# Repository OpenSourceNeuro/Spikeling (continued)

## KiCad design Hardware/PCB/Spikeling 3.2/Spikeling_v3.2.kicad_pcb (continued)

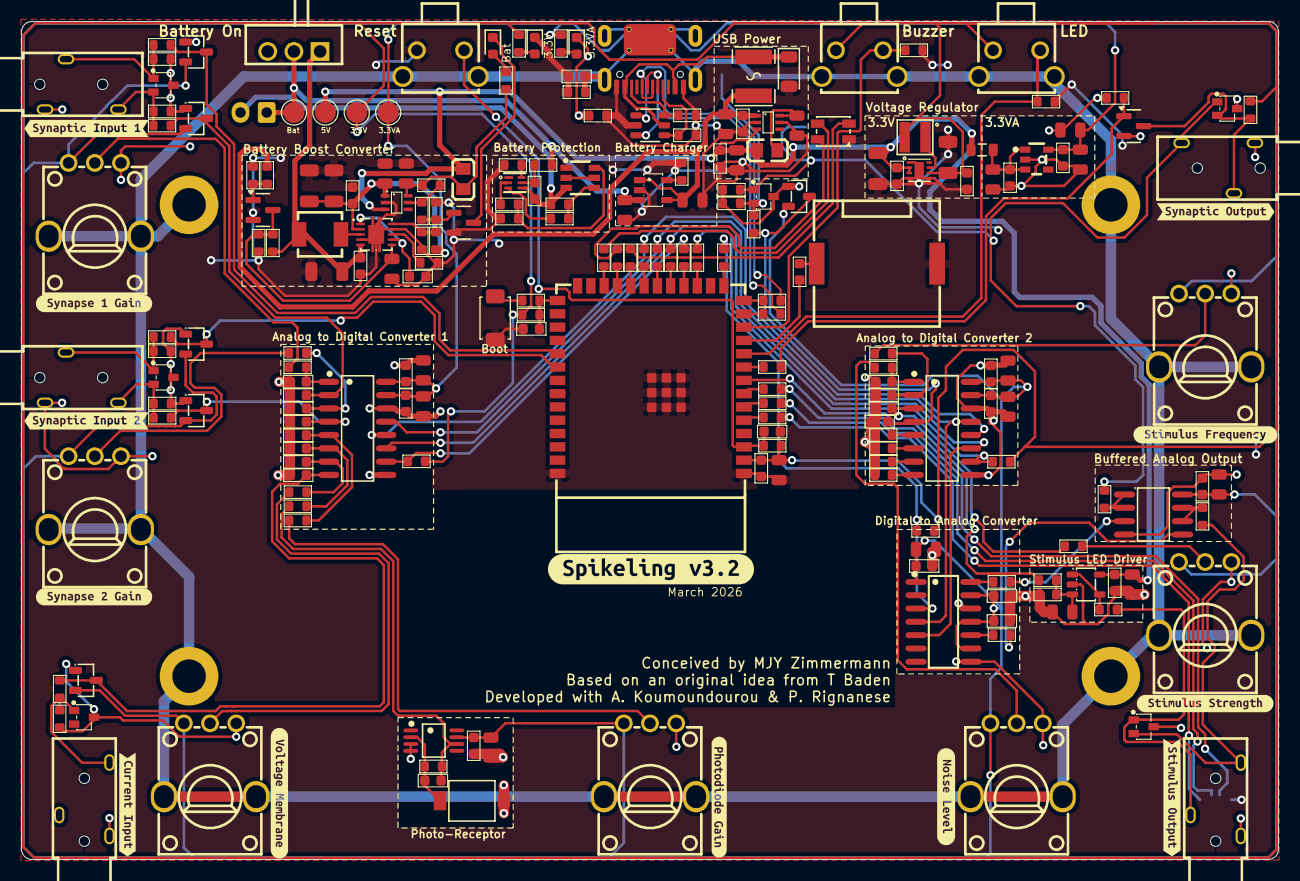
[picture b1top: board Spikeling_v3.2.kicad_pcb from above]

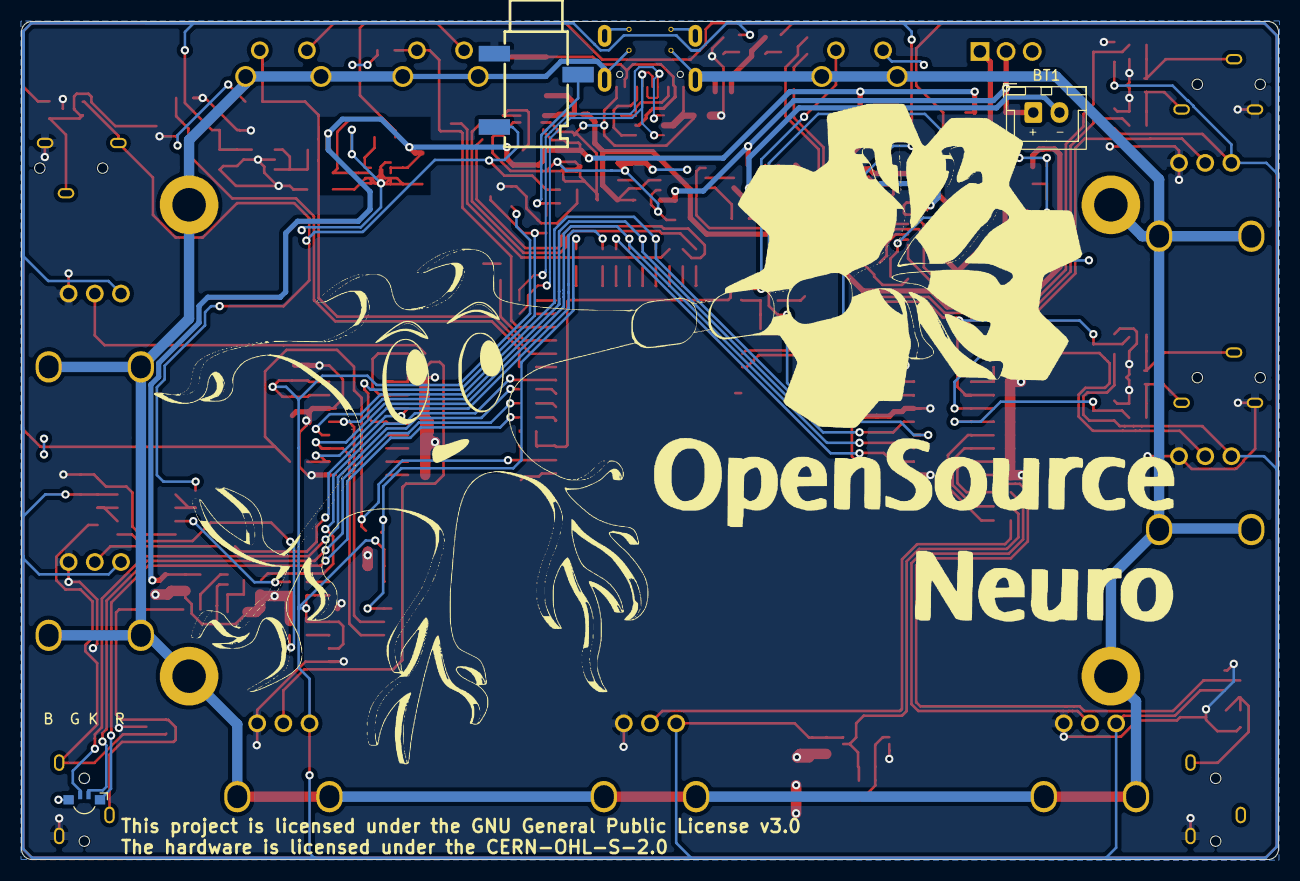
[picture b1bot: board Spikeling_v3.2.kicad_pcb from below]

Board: 2 copper layers, 120.0 x 80.0 mm, 232 parts (3 on the bottom side), 121 nets.

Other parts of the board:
kibuzzard-699ADA5F: G***; kibuzzard-699ADA5F
kibuzzard-699ADA80: G***; kibuzzard-699ADA80
kibuzzard-699ADAA1: G***; kibuzzard-699ADAA1
kibuzzard-699ADACE: G***; kibuzzard-699ADACE
kibuzzard-699ADAEF: G***; kibuzzard-699ADAEF
kibuzzard-699ADB2E: G***; kibuzzard-699ADB2E
kibuzzard-699ADB4A: G***; kibuzzard-699ADB4A
kibuzzard-699ADBA0: G***; kibuzzard-699ADBA0
kibuzzard-699ADBCD: G***; kibuzzard-699ADBCD
kibuzzard-699ADBE4: G***; kibuzzard-699ADBE4
kibuzzard-699ADC07: G***; kibuzzard-699ADC07
kibuzzard-699ADC8D: G***; kibuzzard-699ADC8D
kibuzzard-699AE09E: G***; kibuzzard-699AE09E

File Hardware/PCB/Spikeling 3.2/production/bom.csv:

Designator,Footprint,Quantity,Value,LCSC Part #
B1,BUZ-TH_L12.0-W12.0,1,4kHz,C7421651
BT1,JST_XH_B2B-XH-A_1x02_P2.50mm_Vertical,1,Battery_Cell,C265283
"C1, C55",C_0603,2,1nF,C100040
"C10, C12, C13, C18, C21, C23, C27, C28, C3, C30, C32, C33, C35, C37, C39, C42, C44, C45, C47, C49, C51, C53, C56, C57, C58, C6, C60, C62, C64, C8",C_0603,30,100nF,C1591
"C11, C14, C2, C24, C25, C26, C36, C4, C40, C61",C_0805,10,1uF,C28323
"C15, C16, C17, C29, C31, C34, C38, C5, C52, C59",C_0805,10,4.7uF,C694229
"C19, C20, C9",C_1206,3,22uF,C12891
"C22, C7",C_1206,2,10uF,C2171160
C41,C_0805,1,10uF,C2932476
C43,C_0603,1,4.7nF,C53987
"C46, C48, C50, C63",C_0603,4,10nF,C100042
C54,C_0603,1,10pF,C91367
D1,D_SOD-123FL,1,SMF6.0A,C178260
"D10, D12, D19, D6, D7, D9",SOT-23-3_L2.9-W1.3-P1.90-LS2.4-BR,6,BAT54S,C916425
"D11, D14, D17, D18, D5, D8",SC-70-3_L2.0-W1.3-P0.65-LS2.1-BL,6,TPD2E2U06DCKR,C1855726
D13,SENSOR-TH_BPW34S-Z,1,BPW34S-Z,C67891
D15,LED_Kingbright_APFA3010_3x1.5mm_Horizontal,1,LED_BGKR,
D16,LED-SMD_4P-L3.2-W2.8-BL,1,MHPC3528CRGBCT,C2962096
"D2, D3",D_0603,2,Red,C2286
D4,D_0603,1,Yellow,C89811
J1,TYPE-C-SMD_HX-TYPE-C-16PIN,1,"Connector, USB-TYPE-C-16P",C2927039
J2,AUDIO-SMD_HX-PJ-320A-3P-DIP,1,Synapse1 In,C19189087
J3,AUDIO-SMD_HX-PJ-320A-3P-DIP,1,Synapse2 In,C19189087
J4,AUDIO-SMD_HX-PJ-320A-3P-DIP,1,Input Current,C19189087
J5,AUDIO-SMD_HX-PJ-320A-3P-DIP,1,Stimulus Out,C19189087
J6,AUDIO-SMD_HX-PJ-320A-3P-DIP,1,Synapse Out,C19189087
J7,AUDIO-SMD_PJ-320B,1,Oscilloscope Output,C18594
"L1, L5",L0805,2,BLM21PG221SN1D,C85840
L2,IND-SMD_L3.0-W3.0_XFL3012,1,2.2uH,C3911432
L3,L_0805,1,MPZ2012S601,C21519
L4,IND-SMD_L4.4-W4.0_PHC0420,1,2.2uH,C5349665
Q1,SOT-23-6_L2.9-W1.6-P0.95-LS2.8-BR,1,FS8205A,C908265
"Q2, Q3, Q4",Q_SOT-23,3,2N7002,C8545
"R1, R16, R18, R24, R61",R_0603,5,1MΩ,C105578
"R10, R8",R_0603,2,5.1MΩ,C227984
"R11, R23, R26, R27, R45, R69, R70, R71, R72, R73, R74, R9",R_0603,12,100Ω,C115420
R12,R_0603,1,2.2kΩ,C4190
R13,R_0603,1,330Ω,C23138
R14,R_0603,1,910kΩ,C2907075
"R15, R17, R19, R20, R21, R31, R32, R33, R34, R48, R49, R53, R54, R59, R67, R77, R80, R81",R_0603,18,100kΩ,C14675
"R2, R22, R3, R4, R5",R_0603,5,5.1kΩ,C23186
"R25, R30, R35, R44, R46, R66, R75, R78, R79",R_0603,9,10kΩ,C2906982
"R28, R29",R_0603,2,220Ω,C22962
"R36, R37",R_0603,2,22Ω,C23345
"R38, R39, R40, R41, R42, R43",R_0603,6,47Ω,C23182
"R47, R50, R51, R52, R55, R56, R57, R58, R60, R62, R63, R64, R65, R76, R82",R_0603,15,1kΩ,C2907002
R6,R_0603,1,0Ω,C21189
R68,R_0603,1,150Ω,C22808
R7,R_0603,1,4.7kΩ,C23162
SW1,SW-TH_K3-1260D-L1,1,K3-1260D-L1,C92657
SW2,SW_TS-1088-AR02016,1,"Tactile Button, 160gf",C720477
"SW3, SW4, SW5",KEY-TH_4P-L7.5-W6.8-P4.50-LS7.2,3,SKHHLVA010, C2845277
"TP1, TP2, TP3, TP4",TestPoint_Pad_D2.0mm,4,TestPoint,
TV1,SOT-23-6_L2.9-W1.6-P0.95-LS2.8-BR,1,SRV05-4-P-T7,C85364
U1,F1812,1,MF-MSMF050-2,C17313
"U10, U11",SOIC-16_L9.9-W3.9-P1.27-LS6.0-BL,2,MCP3208T-CI/SL,C626764
U12,WIFIM-SMD_ESP32-S3-WROOM-1-N8,1,ESP32-S3-WROOM-1-N4,C2913197
U13,VSSOP-8_L3.0-W3.0-P0.65-LS4.9-BL,1,OPA380AIDGKR,C2057355
U14,SOT-23-5_L3.0-W1.7-P0.95-LS2.8-BR,1,TLV9001IDBVR,C398363
U15,SOIC-8_L4.9-W3.9-P1.27-LS6.0-BL,1,MCP6002T-I/SN,C7377
"U2, U8",SC-70-6_L2.0-W1.3-P0.65-LS2.1-BL,2,LM66100DCKR,C2869734
U3,WSON-8_L2.0-W2.0-P0.50-TL-EP,1,TPS62162DSGR,C40256
U4,SOT-23-5_L2.9-W1.6-P0.95-LS2.8-BR,1,TPS7A2033PDBVR,C2862740
U5,SOT-23-5_L3.0-W1.7-P0.95-LS2.8-BR,1,MCP73812T-420I/OT,C144308
U6,WSON-6_L1.5-W1.5-P0.50-TL,1,BQ29700DSER,C183096
U7,VSON-10_L3.0-W3.0-P0.50-TL-EP_TPS62410DRCR,1,TPS61200DRCR,C140320
U9,SOIC-14_L8.7-W3.9-P1.27-LS6.0-BL,1,MCP4922-E/SL,C39851
"VR1, VR2, VR3, VR4, VR6, VR7",RES-TH_RK09D1130C2P,6,10kΩ,C470316
VR5,RES-TH_RK09D1130C2P,1,10kΩ,C361173

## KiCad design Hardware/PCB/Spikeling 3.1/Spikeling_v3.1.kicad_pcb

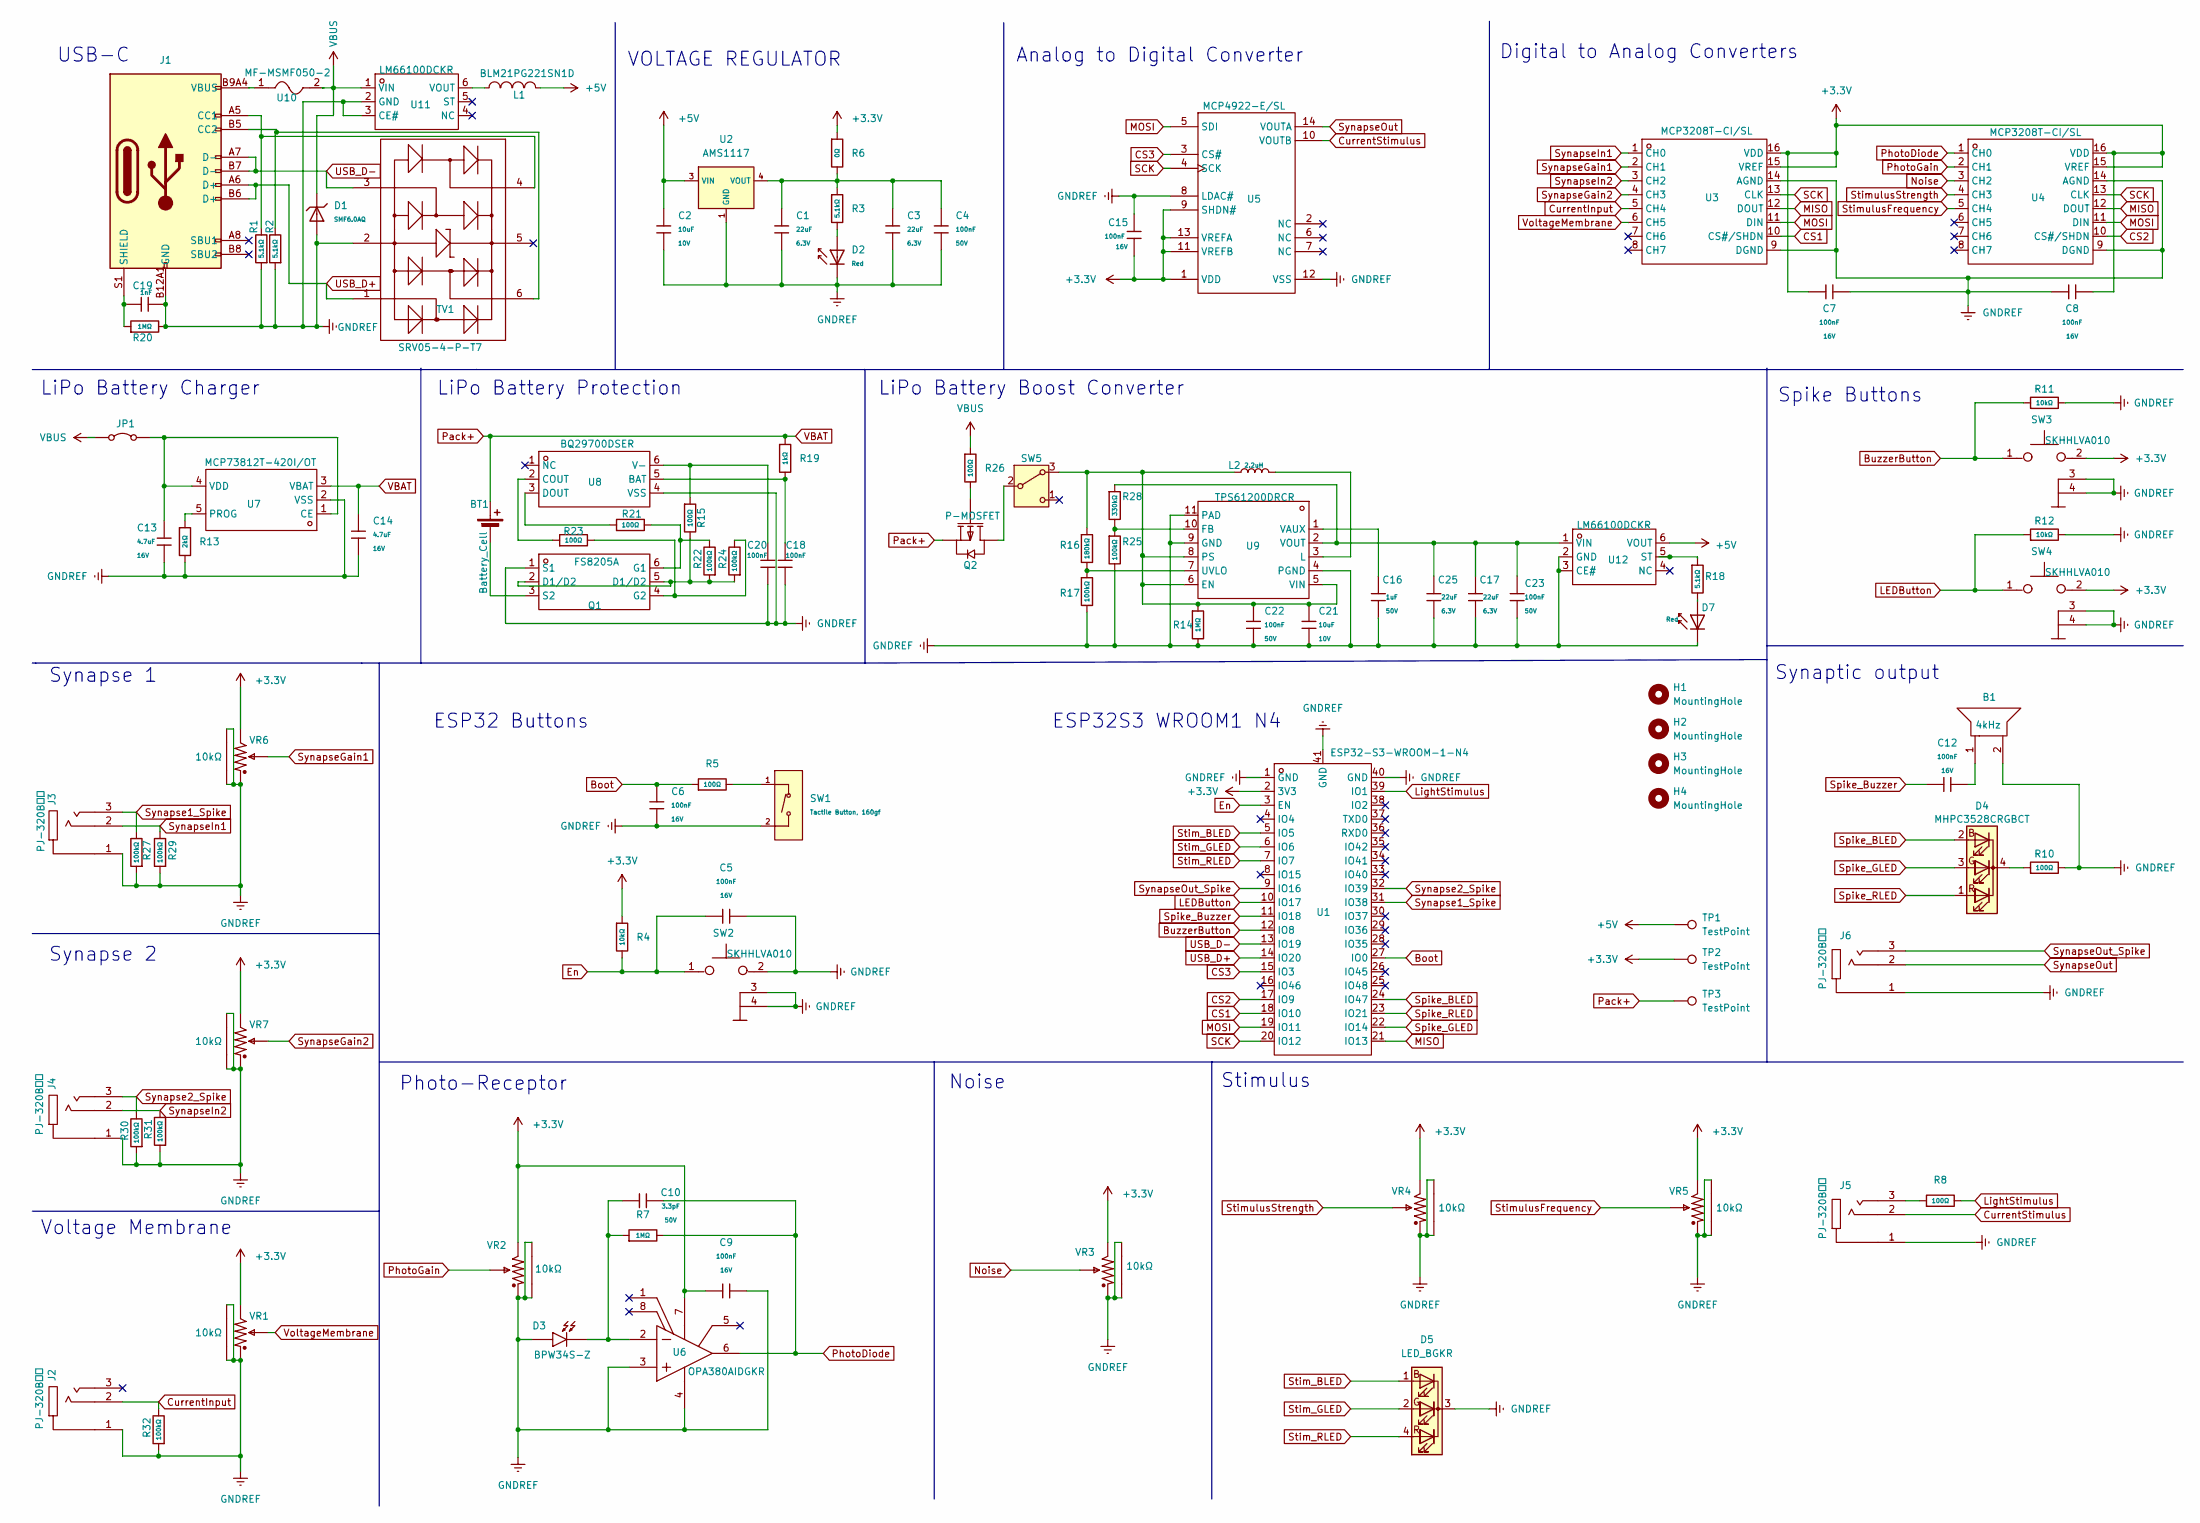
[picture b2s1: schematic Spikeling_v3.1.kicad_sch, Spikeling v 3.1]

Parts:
B1: 4kHz; BUZ-TH_L12.0-W12.0; LCSC Part # C7421651
BT1: Battery_Cell; JST_XH_B2B-XH-A_1x02_P2.50mm_Vertical; LCSC Part # C265283
C1, C3, C17, C25: 22uF; C_0603; Voltage Rated 6.3V; Tolerance ±20%; Part CL10A226MQ8NRNC; LCSC C59461
C2, C21: 10uF; C_0603; Voltage Rated 10V; Tolerance ±10%; Part CL10A106KP8NNNC; LCSC C19702
C4, C18, C20, C22, C23: 100nF; C_0603; Voltage Rated 50V; Tolerance ±10%; Part CC0603KRX7R9BB104; LCSC C14663
C5, C6, C7, C8, C9, C12, C15: 100nF; C_0402; Voltage Rated 16V; Tolerance ±10%; Part CL05B104KO5NNNC; LCSC C1525
C10: 3.3pF; C_0402; Voltage Rated 50V; Part 0402CG3R3C500NT; LCSC C1565
C13, C14: 4.7uF; C_0603; Voltage Rated 16V; Tolerance ±10%; Part CL10A475KO8NNNC; LCSC C19666
C16: 1uF; C_0603; Voltage Rated 50V; Tolerance ±10%; Part CL10A105KB8NNNC; LCSC C15849
C19: 1nF; C_0603; Voltage Rated 50V; Tolerance ±10%; Part CL10B102KB8NNNC; LCSC C1588
D1: SMF6.0AQ; D_SOD-123FL; Part SMF6.0AQ; LCSC Part # C20605188
D2, D7: Red; D_0603; Part KT-0603R; LCSC Part # C2286
D3: BPW34S-Z; SENSOR-TH_BPW34S-Z; MANUFACTURER PART BPW34S-Z; LCSC PART NAME 920nm 频谱范围420nm~1120nm 反向电压32V
D4: MHPC3528CRGBCT; LED-SMD_4P-L3.2-W2.8-BL; LCSC PART NAME RGB三色 正贴
D5: LED_BGKR; LED_D5.0mm-4_RGB_Wide_Pins
H1, H2, H3, H4: MountingHole; MountingHole_3mm
J1: Connector, USB-TYPE-C-16P; TYPE-C-SMD_HX-TYPE-C-16PIN; LCSC Part # C2927039
J2, J3, J4, J5, J6: PJ-320B贴片; AUDIO-SMD_PJ-320B; CURRENT RATING (MAX) 200mA; VOLTAGE RATING (MAX) 30V; MANUFACTURER PART PJ-320B贴片; LCSC PART NAME 3.5mm耳机座
JP1: Jumper; SolderJumper-2_P1.3mm_Open_Pad1.0x1.5mm
L1: BLM21PG221SN1D; L0805; TOLERANCE ±25%; CURRENT RATING 2A; MANUFACTURER PART BLM21PG221SN1D; LCSC PART NAME 单路 0805磁珠 阻抗220Ω@100MHz
L2: 2.2uH; L_0805; Tolerance ±10%; Part CMI201209U2R2KT; LCSC C1043
Q1: FS8205A; SOT-23-6_L2.9-W1.6-P0.95-LS2.8-BR; MANUFACTURER PART FS8205A; LCSC PART NAME 2个N沟道 耐压:20V 电流:6A
Q2: P-MOSFET; SOT-23-3_L2.9-W1.3-P1.90-LS2.4-BR; MANUFACTURER PART SI2309CDS-T1-GE3; LCSC PART NAME 1个P沟道 耐压:60V 电流:1.6A
R1, R2, R3, R18: 5.1kΩ; R_0603; Overload Voltage (Max) 75V; Tolerance ±1%; Part 0603WAF5101T5E; LCSC C23186
R4, R11, R12: 10kΩ; R_0603; Overload Voltage (Max) 75V; Tolerance ±1%; Part 0603WAF1002T5E; LCSC C25804
R5, R8, R10, R15, R21, R23, R26: 100Ω; R_0603; Overload Voltage (Max) 75V; Tolerance ±1%; Part 0603WAF1000T5E; LCSC C22775
R6: 0Ω; R_0603; Overload Voltage (Max) 75V; Tolerance ±1%; Part 0603WAF0000T5E; LCSC C21189
R7, R14, R20: 1MΩ; R_0603; Overload Voltage (Max) 75V; Tolerance ±1%; Part 0603WAF1004T5E; LCSC C22935
R13: 2kΩ; R_0603; Overload Voltage (Max) 75V; Tolerance ±1%; Part 0603WAF2001T5E; LCSC C22975
R16: 180kΩ; R_0603; Overload Voltage (Max) 75V; Tolerance ±1%; Part 0603WAF1803T5E; LCSC C22827
R17, R22, R24, R25, R27, R29, R30, R31, R32: 100kΩ; R_0603; Overload Voltage (Max) 75V; Tolerance ±1%; Part 0603WAF1003T5E; LCSC C25803
R19: 1kΩ; R_0603; Overload Voltage (Max) 75V; Tolerance ±1%; Part 0603WAF1001T5E; LCSC C21190
R28: 330kΩ; R_0603; Overload Voltage (Max) 75V; Tolerance ±1%; Part 0603WAF3303T5E; LCSC C23137
SW1: Tactile Button, 160gf; SW_TS-1088-AR02016; Voltage Rating (Dc) 12V; Part TS-1088-AR02016; LCSC Part # C720477
SW2, SW3, SW4: SKHHLVA010; KEY-TH_4P-L7.5-W6.8-P4.50-LS7.2; VOLTAGE RATING (DC) 12V; MANUFACTURER PART SKHHLVA010; LCSC PART NAME 6*6*5.85mm 卧插 轻触开关
SW5: SW_Nidec_CAS-120A1; SW-TH_MMP122-R; LCSC Part # C92657
TP1, TP2, TP3: TestPoint; TestPoint_Pad_D2.0mm
TV1: SRV05-4-P-T7; SOT-23-6_L2.9-W1.6-P0.95-LS2.8-BR; CLAMPING VOLTAGE 12V; VOLTAGE - BREAKDOWN 6V; MANUFACTURER PART SRV05-4-P-T7; LCSC Part ESD 5V截止 峰值浪涌电流：1A@8/20us
U1: ESP32-S3-WROOM-1-N4; WIFIM-SMD_ESP32-S3-WROOM-1-N8; MANUFACTURER PART ESP32-S3-WROOM-1-N4; LCSC PART NAME 通用型Wi-Fi+低功耗蓝牙MCU模组
U2: AMS1117; SOT-223-3_L6.5-W3.4-P2.30-LS7.0-BR; Output Voltage 3.3V; Dropout Voltage 1.3V@(800mA); Part AMS1117-3.3; LCSC Part # C6186
U3, U4: MCP3208T-CI/SL; SOIC-16_L9.9-W3.9-P1.27-LS6.0-BL; VOLTAGE - SUPPLY 2.7V~5.5V; MANUFACTURER PART MCP3208T-CI/SL; LCSC PART NAME MCP3208T-CI/SL
U5: MCP4922-E/SL; SOIC-14_L8.7-W3.9-P1.27-LS6.0-BL; VOLTAGE - SUPPLY 2.7V~5.5V; VOLTAGE REFERENCE External; MANUFACTURER PART MCP4922-E/SL; LCSC PART NAME MCP4922-E/SL
U6: OPA380AIDGKR; VSSOP-8_L3.0-W3.0-P0.65-LS4.9-BL; MANUFACTURER PART OPA380AIDGKR; LCSC PART NAME OPA380AIDGKR
U7: MCP73812T-420I/OT; SOT-23-5_L3.0-W1.7-P0.95-LS2.8-BR; VOLTAGE - SUPPLY 3.75V~6V; MANUFACTURER PART MCP73812T-420I/OT; LCSC PART NAME 单节锂离子/聚合物电池充电管理控制器
U8: BQ29700DSER; WSON-6_L1.5-W1.5-P0.50-TL; VOLTAGE - SUPPLY -300mV~8V; MANUFACTURER PART BQ29700DSER; LCSC PART NAME BQ29700DSER
U9: TPS61200DRCR; VSON-10_L3.0-W3.0-P0.50-TL-EP_TPS62410DRCR; VOLTAGE - SUPPLY 300mV~5.5V; OUTPUT VOLTAGE 1.8V~5.5V; MANUFACTURER PART TPS61200DRCR; LCSC PART NAME 低输入电压同步升压转换器
U10: MF-MSMF050-2; F1812; VOLTAGE - MAX 15V; MANUFACTURER PART MF-MSMF050-2; LCSC PART NAME 15V 500mA 1812自恢复
U11, U12: LM66100DCKR; SC-70-6_L2.0-W1.3-P0.65-LS2.1-BL; MANUFACTURER PART LM66100DCKR; LCSC PART NAME 5.5V 1.5A 低静态电流理想二极管
VR1, VR2, VR4, VR5, VR6, VR7: 10kΩ; RES-TH_RK09D1130C2P; TOLERANCE ±20%; VOLTAGE RATING 20V; MANUFACTURER PART RK09D1130C3C; LCSC PART NAME 10kΩ ±20%
VR3: 10kΩ; RES-TH_RK09D1130C2P; TOLERANCE ±20%; MANUFACTURER PART RK09D1130C2P; LCSC PART NAME 10kΩ ±20%

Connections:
+3.3V: C7.1, C8.2, C9.1, C15.2, R4.1, R6.1, SW3.2, SW4.2, TP2.1, U1.2 (3V3), U3.15 (VREF), U3.16 (VDD), U4.15 (VREF), U4.16 (VDD), U5.1 (VDD), U5.9 (SHDN#), U5.11 (VREFB), U5.13 (VREFA), U6.7 (V+), VR1.3, VR2.3, VR3.3, VR4.3, VR5.3, VR6.3, VR7.3
+5V: C2.1, L1.2, TP1.1, U2.3 (VIN), U12.6 (VOUT)
Boot: C6.1, R5.1, U1.27 (IO0)
BuzzerButton: R11.1, SW3.1, U1.12 (IO8)
CS1: U1.18 (IO10), U3.10 (CS#/SHDN)
CS2: U1.17 (IO9), U4.10 (CS#/SHDN)
CS3: U1.15 (IO3), U5.3 (CS#)
CurrentInput: J2.2, R32.2, U3.5 (CH4)
CurrentStimulus: J5.2, U5.10 (VOUTB)
En: C5.1, R4.2, SW2.1, U1.3 (EN)
GNDREF: B1.2, C1.2, C2.2, C3.2, C4.2, C5.2, C6.2, C7.2, C8.1, C9.2, C13.2, C14.2, C15.1, C16.2, C17.2, C18.2, C19.2, C20.2, C21.2, C22.2, C23.2, C25.2, D1.2, D2.1, D3.1 (A), D5.3 (K), D7.1, J1.A12B1 (GND), J1.B12A1 (GND), J2.1, J3.1, J4.1, J5.1, J6.1, Q1.1 (S1), R1.1, R2.1, R10.2, R11.2, R12.2, R13.2, R14.2, R17.2, R20.2, R25.2, R27.1, R29.1, R30.1, R31.1, R32.1, SW1.2 (B), SW2.2, SW2.3, SW2.4, SW3.3, SW3.4, SW4.3, SW4.4, TV1.2, U1.1 (GND), U1.40 (GND), U1.41 (GND), U2.1 (GND), U3.9 (DGND), U3.14 (AGND), U4.9 (DGND), U4.14 (AGND), U5.8 (LDAC#), U5.12 (VSS), U6.3 (IN+), U6.4 (V-), U7.2 (VSS), U8.4 (VSS), U9.4 (PGND), U9.9 (GND), U9.11 (PAD), U11.2 (GND), U11.3 (CE#), U12.2 (GND), U12.3 (CE#), VR1.1, VR1.4, VR1.5, VR2.1, VR2.4, VR2.5, VR3.1, VR3.4, VR3.5, VR4.1, VR4.4, VR4.5, VR5.1, VR5.4, VR5.5, VR6.1, VR6.4, VR6.5, VR7.1, VR7.4, VR7.5
LEDButton: R12.1, SW4.1, U1.10 (IO17)
LightStimulus: R8.2, U1.39 (IO1)
MISO: U1.21 (IO13), U3.12 (DOUT), U4.12 (DOUT)
MOSI: U1.19 (IO11), U3.11 (DIN), U4.11 (DIN), U5.5 (SDI)
unnamed: B1.1, C12.2
unnamed: BT1.2 (-), Q1.3 (S2)
unnamed: C1.1, C3.1, C4.1, R3.1, R6.2, U2.2 (VOUT), U2.4 (VOUT)
unnamed: D2.2, R3.2
unnamed: C10.2, D3.2 (C), R7.1, U6.2 (IN-)
unnamed: D4.4 (K), R10.1
unnamed: D7.2, R18.2
unnamed: J1.A5 (CC1), R1.2, TV1.4
unnamed: J1.B5 (CC2), R2.2, TV1.6
unnamed: C19.1, J1.S1 (SHIELD), R20.1
unnamed: J1.A9B4 (VBUS), J1.B9A4 (VBUS), U10.1
unnamed: J5.3, R8.1
unnamed: C13.1, JP1.2 (B), U7.1 (CE), U7.4 (VDD)
unnamed: Q1.2 (D1/D2), Q1.5 (D1/D2), R15.2, R22.1, R24.1
unnamed: Q1.4 (G2), R23.2, R24.2
unnamed: Q2.3 (D), SW5.2 (B)
unnamed: Q2.1 (G), R26.2
unnamed: R5.2, SW1.1 (A)
unnamed: C21.1, C22.1, L2.1, R14.1, R16.1, SW5.3 (A), U9.5 (VIN), U9.6 (EN), U9.8 (PS)
unnamed: R13.1, U7.5 (PROG)
unnamed: C18.1, R19.2, U8.5 (BAT)
unnamed: R23.1, U8.2 (COUT)
unnamed: C20.1, R15.1, U8.6 (V-)
unnamed: R25.1, R28.2, U9.10 (FB)
unnamed: L2.2, U9.3 (L)
unnamed: R16.2, R17.1, U9.7 (UVLO)
unnamed: C16.1, U9.1 (VAUX)
unnamed: L1.1, U11.6 (VOUT)
unnamed: R18.1, U12.5 (ST)
unnamed: C17.1, C23.1, C25.1, R28.1, U9.2 (VOUT), U12.1 (VIN)
Noise: U4.3 (CH2), VR3.2
PhotoDiode: C10.1, R7.2, U4.1 (CH0), U6.6 (OUT)
PhotoGain: U4.2 (CH1), VR2.2
SCK: U1.20 (IO12), U3.13 (CLK), U4.13 (CLK), U5.4 (SCK)
Spike_BLED: D4.2 (BA), U1.24 (IO47)
Spike_Buzzer: C12.1, U1.11 (IO18)
Spike_GLED: D4.3 (GA), U1.22 (IO14)
Spike_RLED: D4.1 (RA), U1.23 (IO21)
Stim_BLED: D5.1 (BA), U1.5 (IO5)
Stim_GLED: D5.2 (GA), U1.6 (IO6)
Stim_RLED: D5.4 (RA), U1.7 (IO7)
StimulusFrequency: U4.5 (CH4), VR5.2
StimulusStrength: U4.4 (CH3), VR4.2
Synapse1_Spike: J3.3, R27.2, U1.31 (IO38)
Synapse2_Spike: J4.3, R30.2, U1.32 (IO39)
SynapseGain1: U3.2 (CH1), VR6.2
SynapseGain2: U3.4 (CH3), VR7.2
SynapseIn1: J3.2, R29.2, U3.1 (CH0)
SynapseIn2: J4.2, R31.2, U3.3 (CH2)
SynapseOut: J6.2, U5.14 (VOUTA)
SynapseOut_Spike: J6.3, U1.9 (IO16)
USB_D+: J1.A6 (D+), J1.B6 (D+), TV1.1, U1.14 (IO20)
USB_D-: J1.A7 (D-), J1.B7 (D-), TV1.3, U1.13 (IO19)
VBUS: D1.1, JP1.1 (A), R26.1, U10.2, U11.1 (VIN)
VoltageMembrane: U3.6 (CH5), VR1.2

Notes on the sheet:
Spike Buttons
LiPo Battery Charger
Synapse 1
ESP32 Buttons
Synapse 2
LiPo Battery Boost Converter
Digital to Analog Converters
USB-C
Voltage Membrane
LiPo Battery Protection
Noise
Stimulus
Analog to Digital Converter
VOLTAGE REGULATOR
Photo-Receptor
ESP32S3 WROOM1 N4
Synaptic output

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
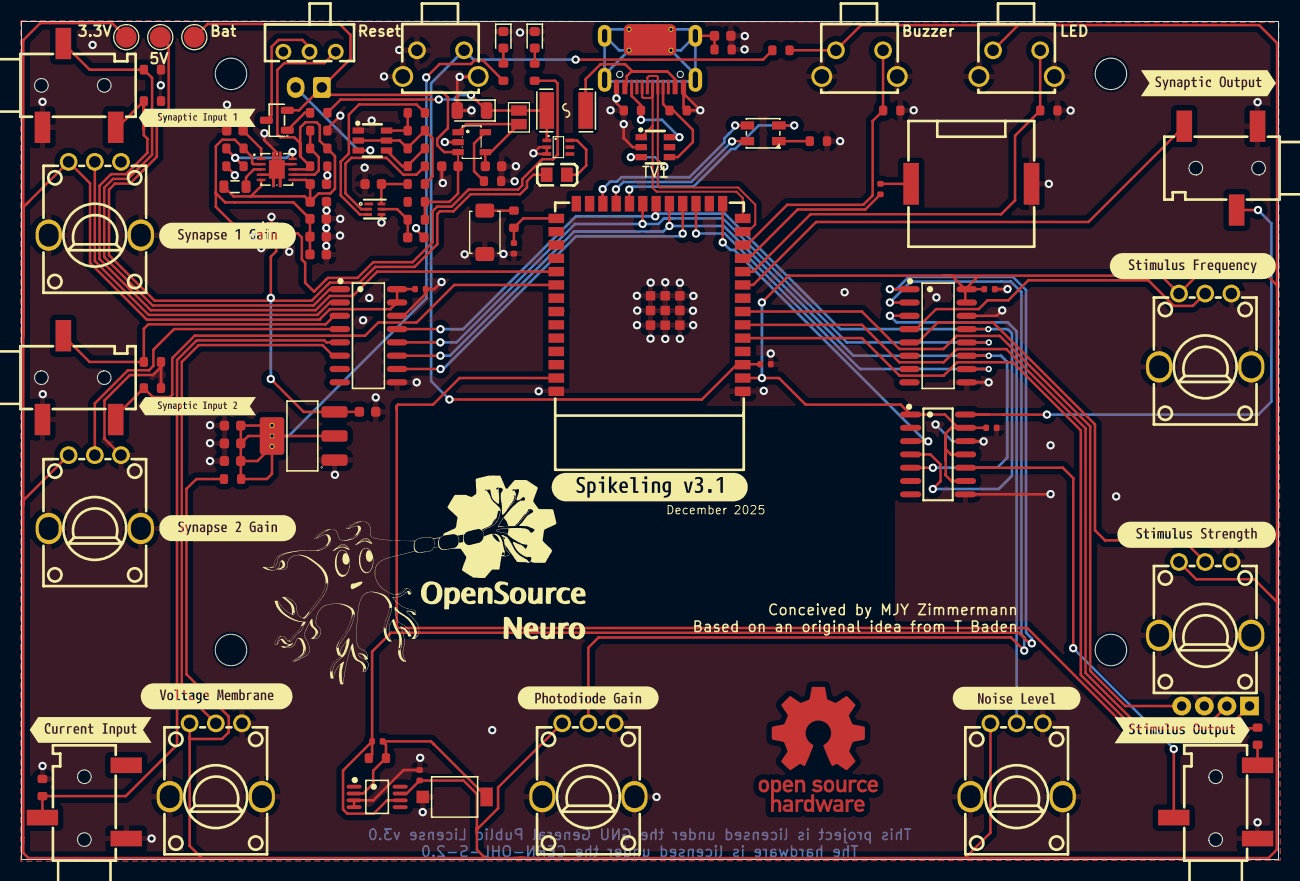
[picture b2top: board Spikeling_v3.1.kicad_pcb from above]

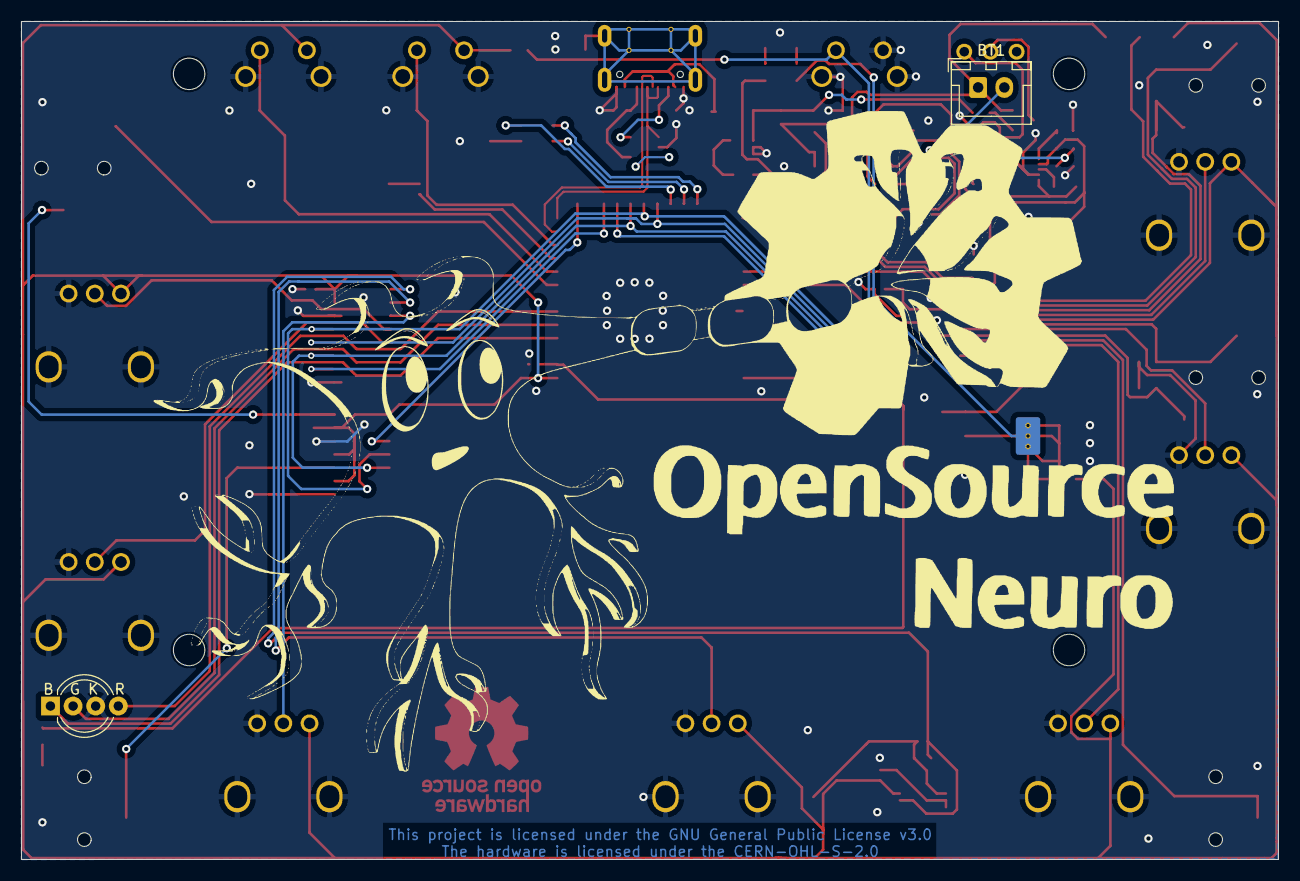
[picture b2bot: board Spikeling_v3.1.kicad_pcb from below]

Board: 2 copper layers, 120.0 x 80.0 mm, 119 parts (2 on the bottom side), 73 nets.

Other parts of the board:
R21#2: 100Ω; R_0603
kibuzzard-6957C67D: G***; kibuzzard-6957C67D
kibuzzard-69554E7A: G***; kibuzzard-69554E7A
kibuzzard-69554E8F: G***; kibuzzard-69554E8F
kibuzzard-69554E9A: G***; kibuzzard-69554E9A
kibuzzard-69554E80: G***; kibuzzard-69554E80
kibuzzard-69554E87: G***; kibuzzard-69554E87
kibuzzard-69554EA3: G***; kibuzzard-69554EA3
kibuzzard-69554EAA: G***; kibuzzard-69554EAA
kibuzzard-69554EC0: G***; kibuzzard-69554EC0
kibuzzard-69554EC6: G***; kibuzzard-69554EC6
kibuzzard-69554ED0: G***; kibuzzard-69554ED0
kibuzzard-689383B5: G***; kibuzzard-689383B5
kibuzzard-68938370: G***; kibuzzard-68938370

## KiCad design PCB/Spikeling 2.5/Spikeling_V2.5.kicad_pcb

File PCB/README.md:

SPDX-License-Identifier: CERN-OHL-S-2.0

This directory contains the hardware design sources (KiCad schematics/PCBs, fabrication outputs).
Copyright (c) 2026 OpenSourceNeuro contributors.

Source Location: https://github.com/OpenSourceNeuro/Spikeling
License text: see PCB/LICENSE (CERN-OHL-S v2)

<h1 align="center"> Spikeling v2 - Assembly Manual</h1></p>

<br></br>

## Overview

<p align="justify">
This page contains detailed assembly instructions for both version of La Spikeling unit, and includes a parts list for purchasing all electronics components.
Instructions on how to upload and update the microcontroller code and how to calibrate the device can be found <a href="https://github.com/OpenSourceNeuro/Spikeling-V2/tree/main/Instruction%20Manual"> <strong>on the instruction manual</strong> </a>.
Instructions regarding the GUI and on how to design stimuli can be found <a href="https://github.com/OpenSourceNeuro/LED-Zappelin-V2/blob/main/GUI_UserManual.md"><strong>here</strong></a>
</p>

***

- [Ordering PCB](#Ordering-the-PCB)
- [Assembling Spikeling](#Assembly)
- [Acrylic Covers](#Acrylic-Covers)

***

## Ordering the PCB

<p align="justify">
First step consist in getting the printed circuit board (PCB).
The PCB source files were designed on <a href="http://kicad.org/">KiCAD 9.0</a> and are available here to be modified by users if need be.
Users can find the "Gerber" files (zipped in the gerber folder) that companies (i.e. <a href="https://jlcpcb.com">JLCPCB</a>) will request to manufacture PCBs.
</p>

<br></br>

***
***

## Assembly

## Acrylic Covers

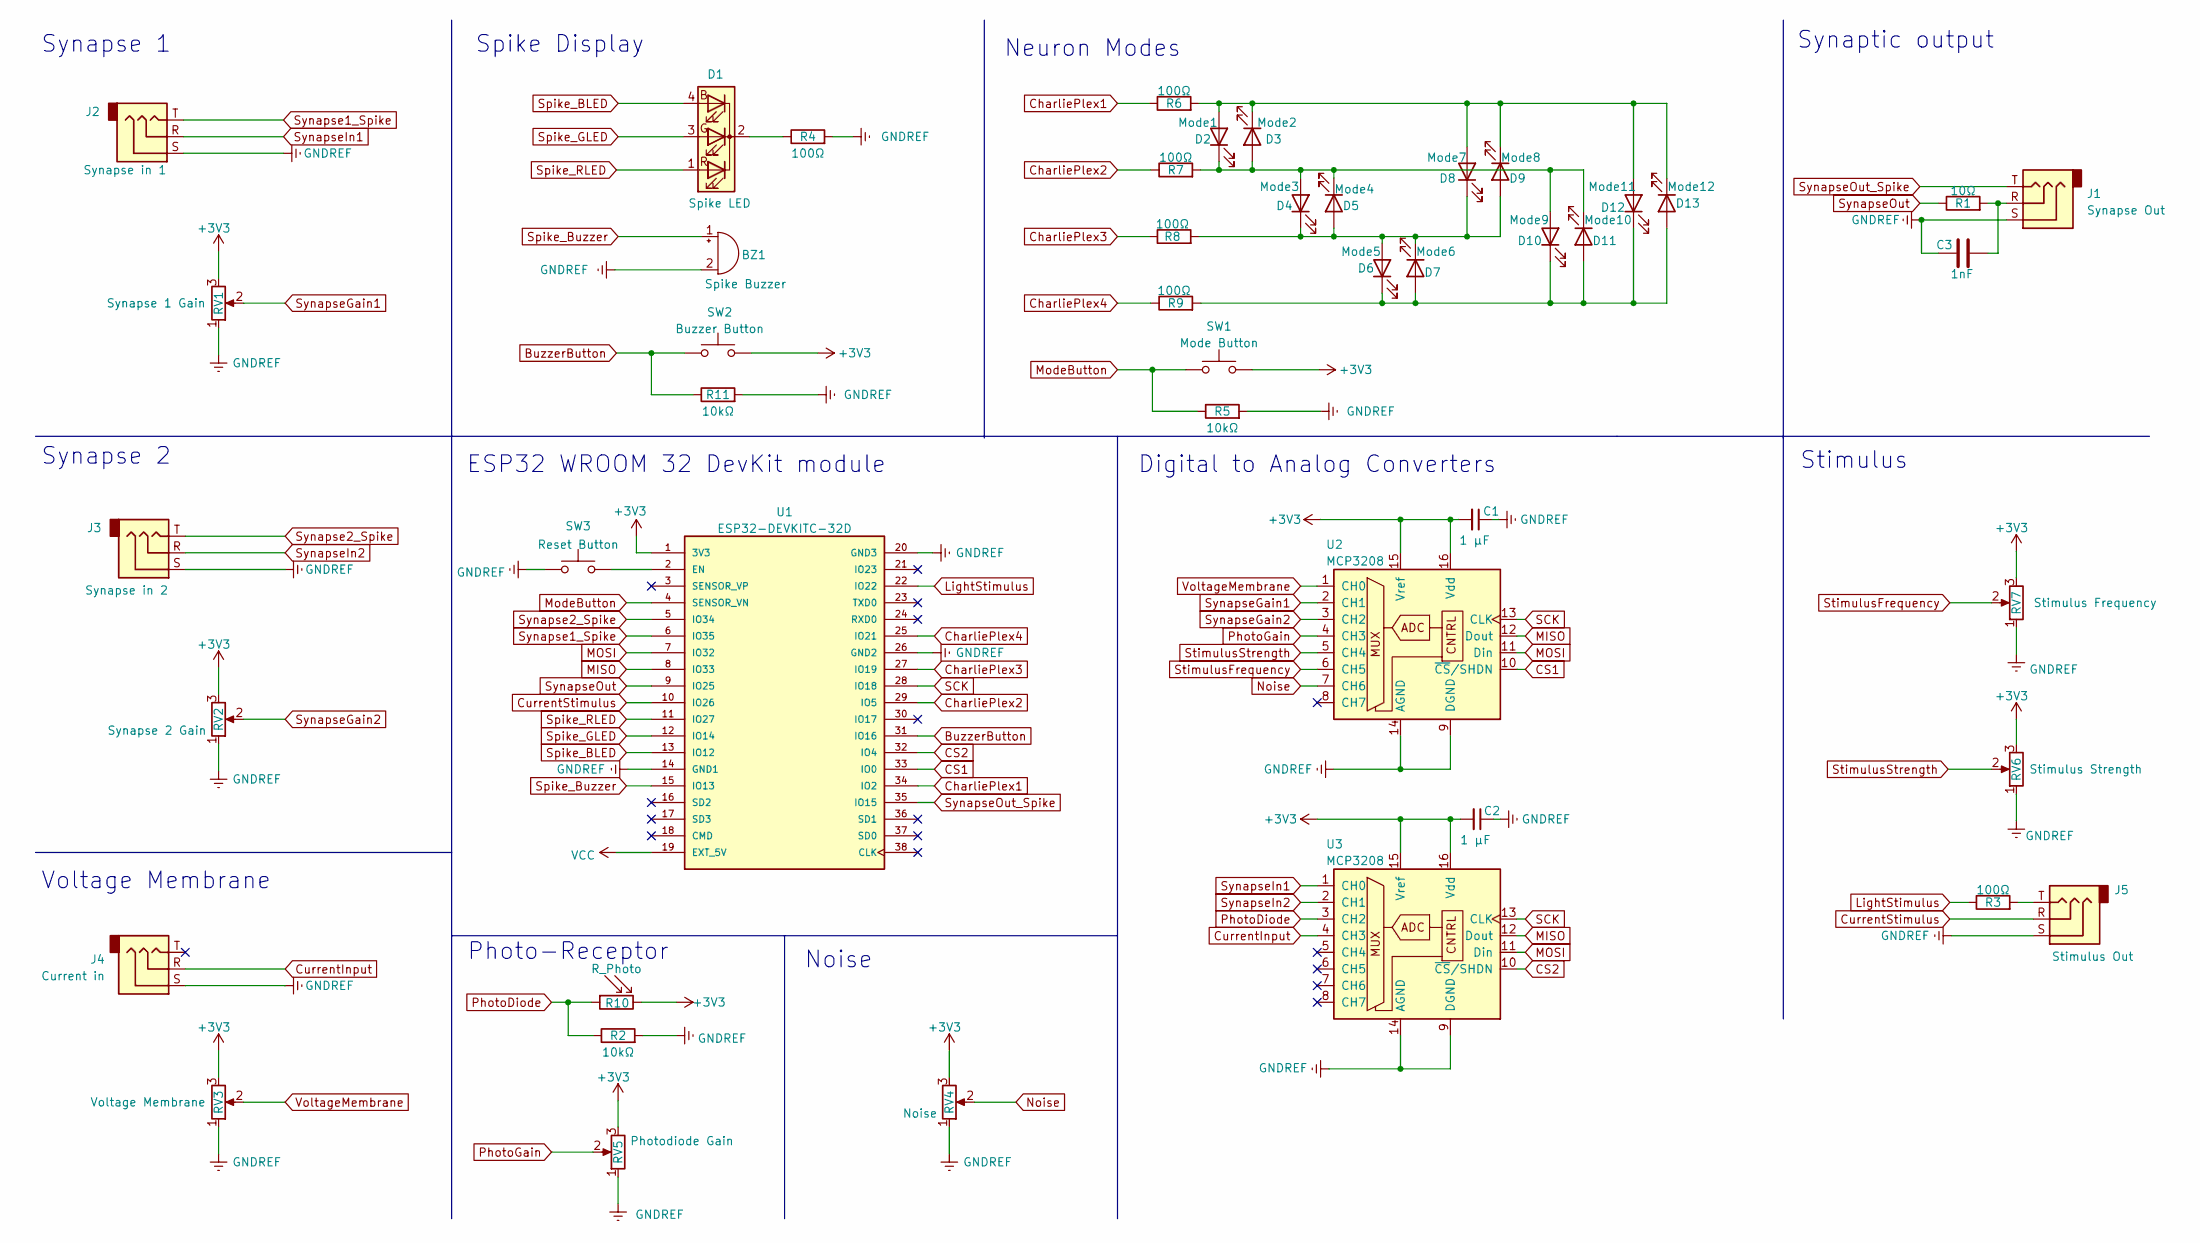
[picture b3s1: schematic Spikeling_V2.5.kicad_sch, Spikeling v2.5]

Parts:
BZ1: Spike Buzzer; Buzzer_11.5x9.5RM5
C1, C2: 1 μF; CP_Radial_D4.0mm_P2.00mm
C3: 1nF; CP_Radial_D4.0mm_P2.00mm
D1: Spike LED; LED_D5.0mm-4_RGB_Wide_Pins
D2: Mode1; LED_D3.0mm
D3: Mode2; LED_D3.0mm
D4: Mode3; LED_D3.0mm
D5: Mode4; LED_D3.0mm
D6: Mode5; LED_D3.0mm
D7: Mode6; LED_D3.0mm
D8: Mode7; LED_D3.0mm
D9: Mode8; LED_D3.0mm
D10: Mode9; LED_D3.0mm
D11: Mode10; LED_D3.0mm
D12: Mode11; LED_D3.0mm
D13: Mode12; LED_D3.0mm
J1: Synapse Out; Spikeling Audio Jack 3.5mm
J2: Synapse in 1; Spikeling Audio Jack 3.5mm
J3: Synapse in 2; Spikeling Audio Jack 3.5mm
J4: Current in; Spikeling Audio Jack 3.5mm
J5: Stimulus Out; Spikeling Audio Jack 3.5mm
R1: 10Ω; R_Axial_DIN0207_L6.3mm_D2.5mm_P10.16mm_Horizontal
R2, R5, R11: 10kΩ; R_Axial_DIN0207_L6.3mm_D2.5mm_P10.16mm_Horizontal
R3, R4, R6, R7, R8, R9: 100Ω; R_Axial_DIN0207_L6.3mm_D2.5mm_P10.16mm_Horizontal
R10: R_Photo; Photoresistor_3.4
RV1: Synapse 1 Gain; Spikeling Potentiometer
RV2: Synapse 2 Gain; Spikeling Potentiometer
RV3: Voltage Membrane; Spikeling Potentiometer
RV4: Noise; Spikeling Potentiometer
RV5: Photodiode Gain; Spikeling Potentiometer
RV6: Stimulus Strength; Spikeling Potentiometer
RV7: Stimulus Frequency; Spikeling Potentiometer
SW1: Mode Button; SW_PUSH_6mm_H13mm
SW2: Buzzer Button; Spikeling reset button
SW3: Reset Button; Spikeling reset button
U1: ESP32-DEVKITC-32D; MODULE_ESP32-DEVKITC-32D; PARTREV 4
U2, U3: MCP3208; DIP-16_W7.62mm

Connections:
+3V3: C1.2, C2.2, R10.2, RV1.3, RV2.3, RV3.3, RV4.3, RV5.3, RV6.3, RV7.3, SW1.2, SW2.2, U1.1 (3V3), U2.15 (Vref), U2.16 (Vdd), U3.15 (Vref), U3.16 (Vdd)
BuzzerButton: R11.1, SW2.1, U1.31 (IO16)
CS1: U1.33 (IO0), U2.10 (~CS/SHDN)
CS2: U1.32 (IO4), U3.10 (~CS/SHDN)
CharliePlex1: R6.1, U1.34 (IO2)
CharliePlex2: R7.1, U1.29 (IO5)
CharliePlex3: R8.1, U1.27 (IO19)
CharliePlex4: R9.1, U1.25 (IO21)
CurrentInput: J4.R, U3.4 (CH3)
CurrentStimulus: J5.R, U1.10 (IO26)
GNDREF: BZ1.2 (+), C1.1, C2.1, C3.1, J1.S, J2.S, J3.S, J4.S, J5.S, R2.2, R4.2, R5.2, R11.2, RV1.1, RV2.1, RV3.1, RV4.1, RV5.1, RV6.1, RV7.1, SW3.1, U1.14 (GND1), U1.20 (GND3), U1.26 (GND2), U2.9 (DGND), U2.14 (AGND), U3.9 (DGND), U3.14 (AGND)
LightStimulus: R3.1, U1.22 (IO22)
MISO: U1.8 (IO33), U2.12 (Dout), U3.12 (Dout)
MOSI: U1.7 (IO32), U2.11 (Din), U3.11 (Din)
ModeButton: R5.1, SW1.1, U1.4 (SENSOR_VN)
unnamed: C3.2, J1.R, R1.2
unnamed: D1.2 (K), R4.1
unnamed: D4.1 (K), D5.2 (A), D6.2 (A), D7.1 (K), D8.1 (K), D9.2 (A), R8.2
unnamed: D2.1 (K), D3.2 (A), D4.2 (A), D5.1 (K), D10.2 (A), D11.1 (K), R7.2
unnamed: D6.1 (K), D7.2 (A), D10.1 (K), D11.2 (A), D12.1 (K), D13.2 (A), R9.2
unnamed: D2.2 (A), D3.1 (K), D8.2 (A), D9.1 (K), D12.2 (A), D13.1 (K), R6.2
unnamed: J5.T, R3.2
unnamed: SW3.2, U1.2 (EN)
Noise: RV4.2, U2.7 (CH6)
PhotoDiode: R2.1, R10.1, U3.3 (CH2)
PhotoGain: RV5.2, U2.4 (CH3)
SCK: U1.28 (IO18), U2.13 (CLK), U3.13 (CLK)
Spike_BLED: D1.4 (BA), U1.13 (IO12)
Spike_Buzzer: BZ1.1 (-), U1.15 (IO13)
Spike_GLED: D1.3 (GA), U1.12 (IO14)
Spike_RLED: D1.1 (RA), U1.11 (IO27)
StimulusFrequency: RV7.2, U2.6 (CH5)
StimulusStrength: RV6.2, U2.5 (CH4)
Synapse1_Spike: J2.T, U1.6 (IO35)
Synapse2_Spike: J3.T, U1.5 (IO34)
SynapseGain1: RV1.2, U2.2 (CH1)
SynapseGain2: RV2.2, U2.3 (CH2)
SynapseIn1: J2.R, U3.1 (CH0)
SynapseIn2: J3.R, U3.2 (CH1)
SynapseOut: R1.1, U1.9 (IO25)
SynapseOut_Spike: J1.T, U1.35 (IO15)
VCC: U1.19 (EXT_5V)
VoltageMembrane: RV3.2, U2.1 (CH0)

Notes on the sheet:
Digital to Analog Converters
Noise
ESP32 WROOM 32 DevKit module
Photo-Receptor
Neuron Modes
Stimulus
Synapse 2
Synaptic output
Spike Display
Synapse 1
Voltage Membrane
